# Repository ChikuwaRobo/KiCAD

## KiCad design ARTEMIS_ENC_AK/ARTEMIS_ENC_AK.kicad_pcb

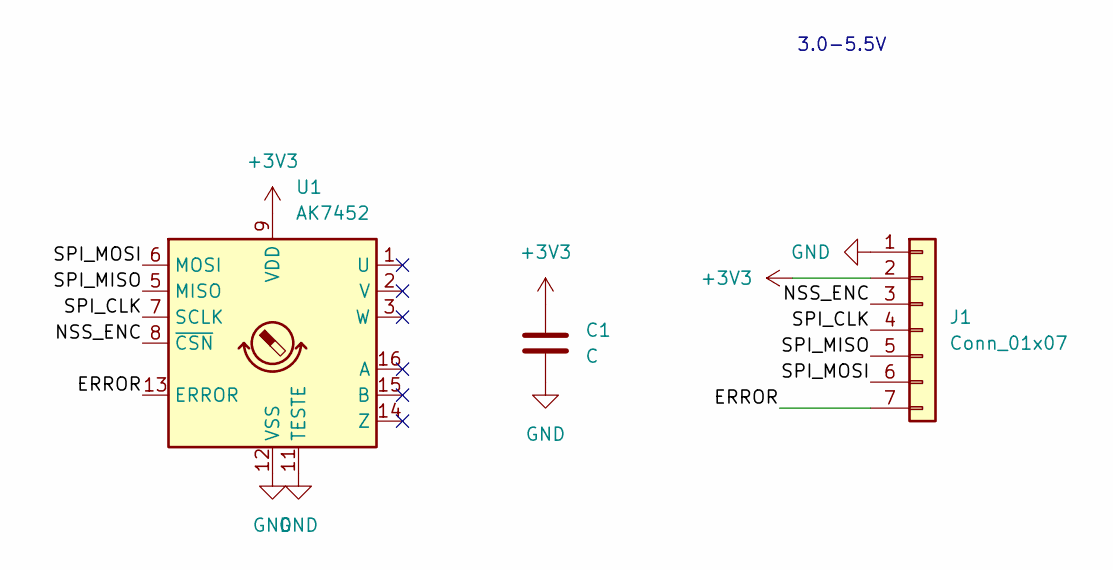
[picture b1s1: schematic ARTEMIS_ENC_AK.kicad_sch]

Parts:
C1: C; C_0603_1608Metric
J1: Conn_01x07; Hirose_DF13-07P-1.25DSA_1x07_P1.25mm_Vertical
U1: AK7452; TSSOP-16_4.4x5mm_P0.65mm

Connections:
+3V3: C1.1, J1.2, U1.9 (VDD)
/ERROR: J1.7, U1.13 (ERROR)
/NSS_ENC: J1.3, U1.8 (~CSN)
/SPI_CLK: J1.4, U1.7 (SCLK)
/SPI_MISO: J1.5, U1.5 (MISO)
/SPI_MOSI: J1.6, U1.6 (MOSI)
GND: C1.2, J1.1, U1.11 (TESTE), U1.12 (VSS)

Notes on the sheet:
3.0-5.5V

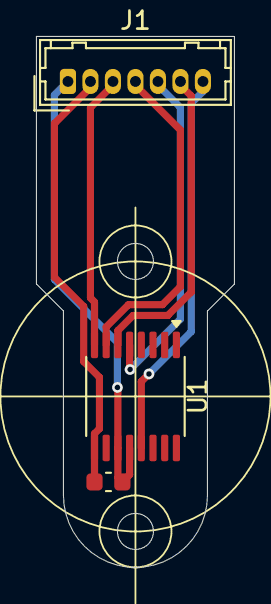
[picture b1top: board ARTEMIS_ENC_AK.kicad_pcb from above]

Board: 2 copper layers, 11.0 x 29.5 mm, 3 parts (0 on the bottom side), 7 nets.

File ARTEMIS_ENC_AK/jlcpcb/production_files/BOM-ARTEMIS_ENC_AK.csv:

Comment,Designator,Footprint,LCSC,Quantity
Conn_01x07,J1,Hirose_DF13-07P-1.25DSA_1x07_P1.25mm_Vertical,,1
AK7452,U1,TSSOP-16_4.4x5mm_P0.65mm,,1
C,C1,C_0603_1608Metric,,1

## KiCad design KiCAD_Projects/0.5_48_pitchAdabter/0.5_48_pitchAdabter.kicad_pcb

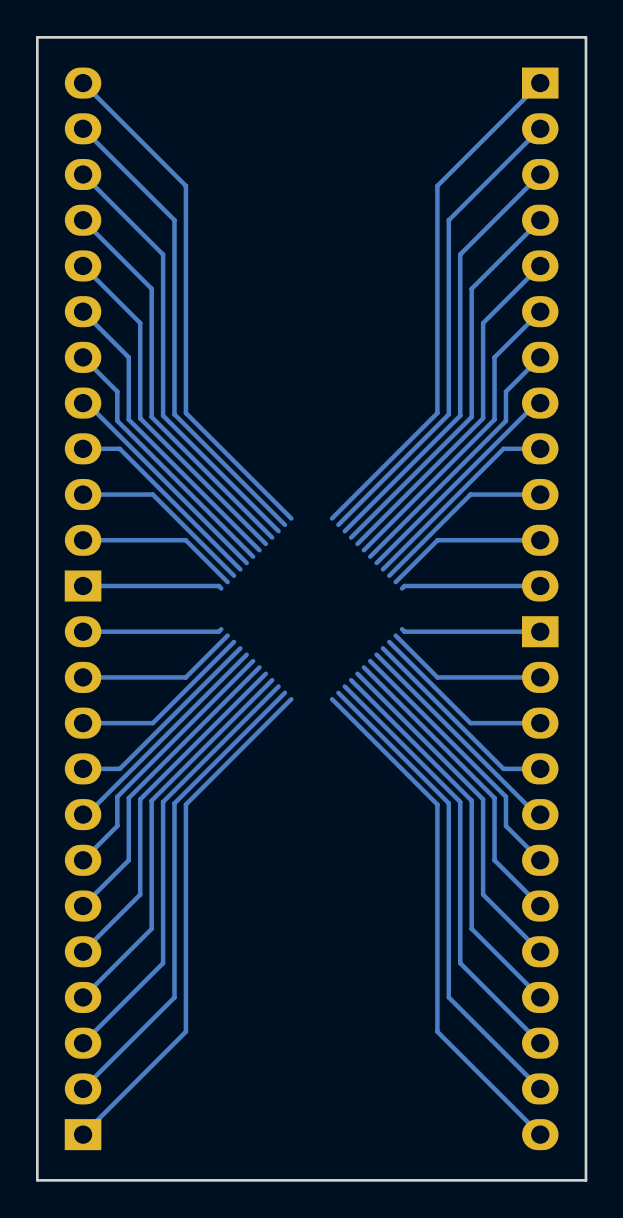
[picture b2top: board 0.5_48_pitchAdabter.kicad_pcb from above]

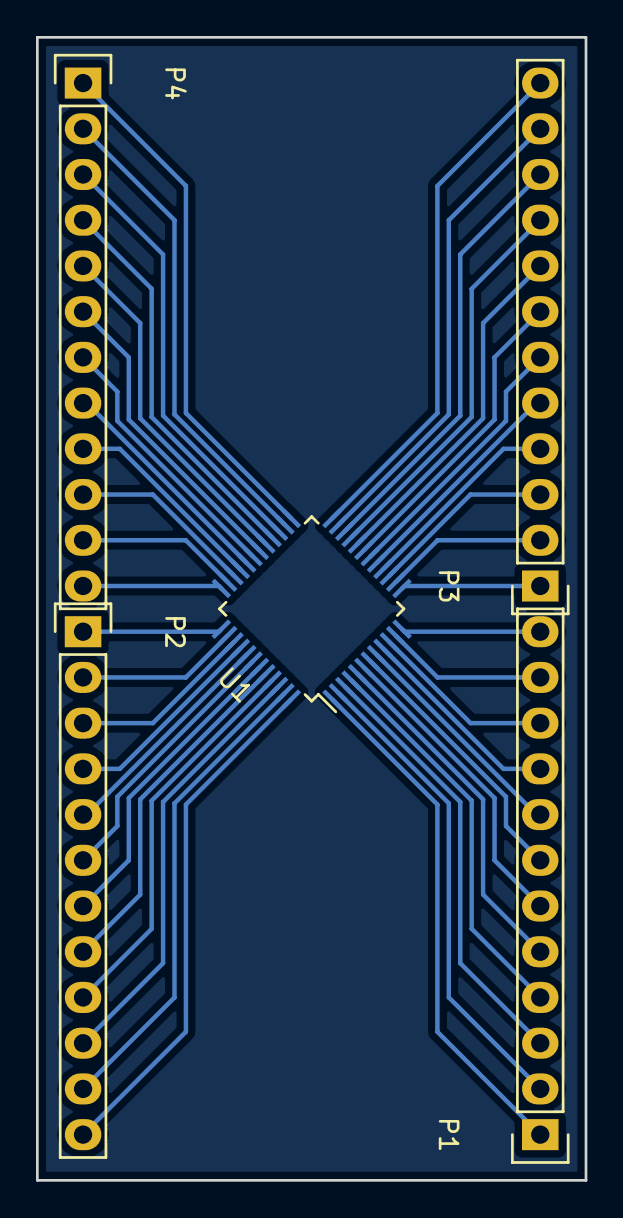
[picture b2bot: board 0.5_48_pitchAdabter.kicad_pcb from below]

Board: 2 copper layers, 30.5 x 63.5 mm, 5 parts (5 on the bottom side), 48 nets.

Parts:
P1, P2, P3, P4: CONN_01X12; Socket_Strip_Straight_1x12
U1: STM32F103_48; TQFP-48_7x7mm_Pitch0.5mm

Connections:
unnamed: P1.1, U1.1
unnamed: P1.2, U1.2
unnamed: P1.3, U1.3
unnamed: P1.4, U1.4
unnamed: P1.5, U1.5
unnamed: P1.6, U1.6
unnamed: P1.7, U1.7
unnamed: P1.8, U1.8
unnamed: P1.9, U1.9
unnamed: P1.10, U1.10
unnamed: P1.11, U1.11
unnamed: P1.12, U1.12
unnamed: P2.1, U1.37
unnamed: P2.2, U1.38
unnamed: P2.3, U1.39
unnamed: P2.4, U1.40
unnamed: P2.5, U1.41
unnamed: P2.6, U1.42
unnamed: P2.7, U1.43
unnamed: P2.8, U1.44
unnamed: P2.9, U1.45
unnamed: P2.10, U1.46
unnamed: P2.11, U1.47
unnamed: P2.12, U1.48
unnamed: P3.1, U1.13
unnamed: P3.2, U1.14
unnamed: P3.3, U1.15
unnamed: P3.4, U1.16
unnamed: P3.5, U1.17
unnamed: P3.6, U1.18
unnamed: P3.7, U1.19
unnamed: P3.8, U1.20
unnamed: P3.9, U1.21
unnamed: P3.10, U1.22
unnamed: P3.11, U1.23
unnamed: P3.12, U1.24
unnamed: P4.1, U1.25
unnamed: P4.2, U1.26
unnamed: P4.3, U1.27
unnamed: P4.4, U1.28
unnamed: P4.5, U1.29
unnamed: P4.6, U1.30
unnamed: P4.7, U1.31
unnamed: P4.8, U1.32
unnamed: P4.9, U1.33
unnamed: P4.10, U1.34
unnamed: P4.11, U1.35
unnamed: P4.12, U1.36

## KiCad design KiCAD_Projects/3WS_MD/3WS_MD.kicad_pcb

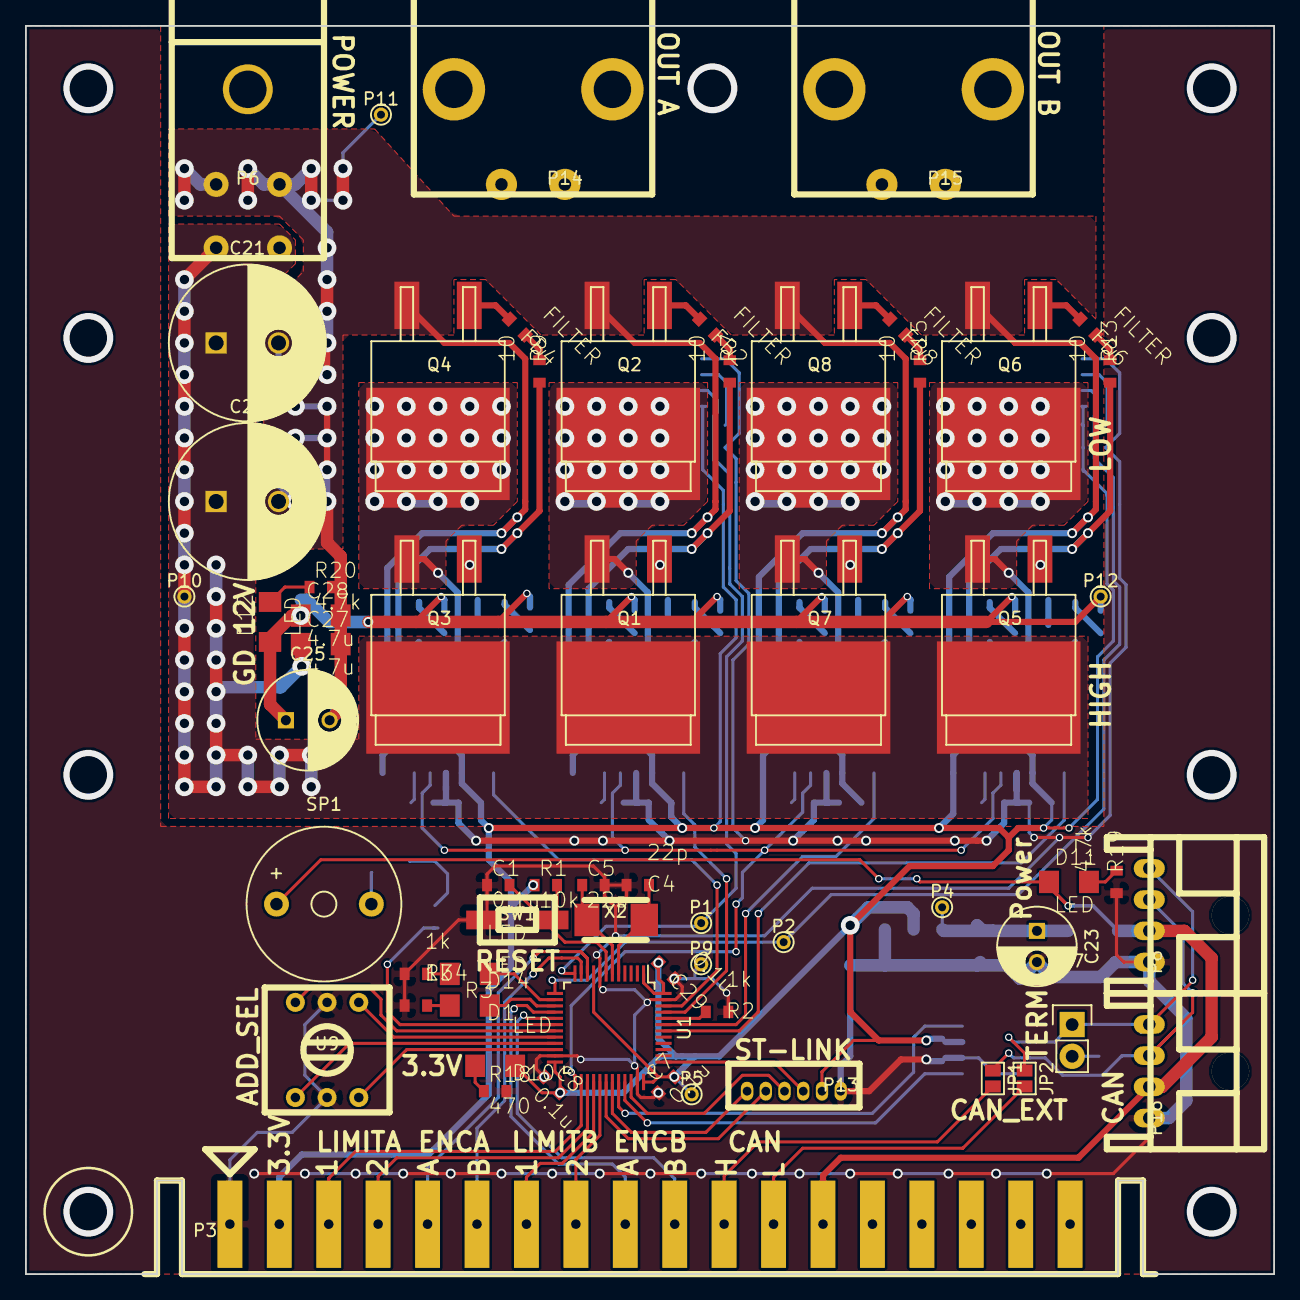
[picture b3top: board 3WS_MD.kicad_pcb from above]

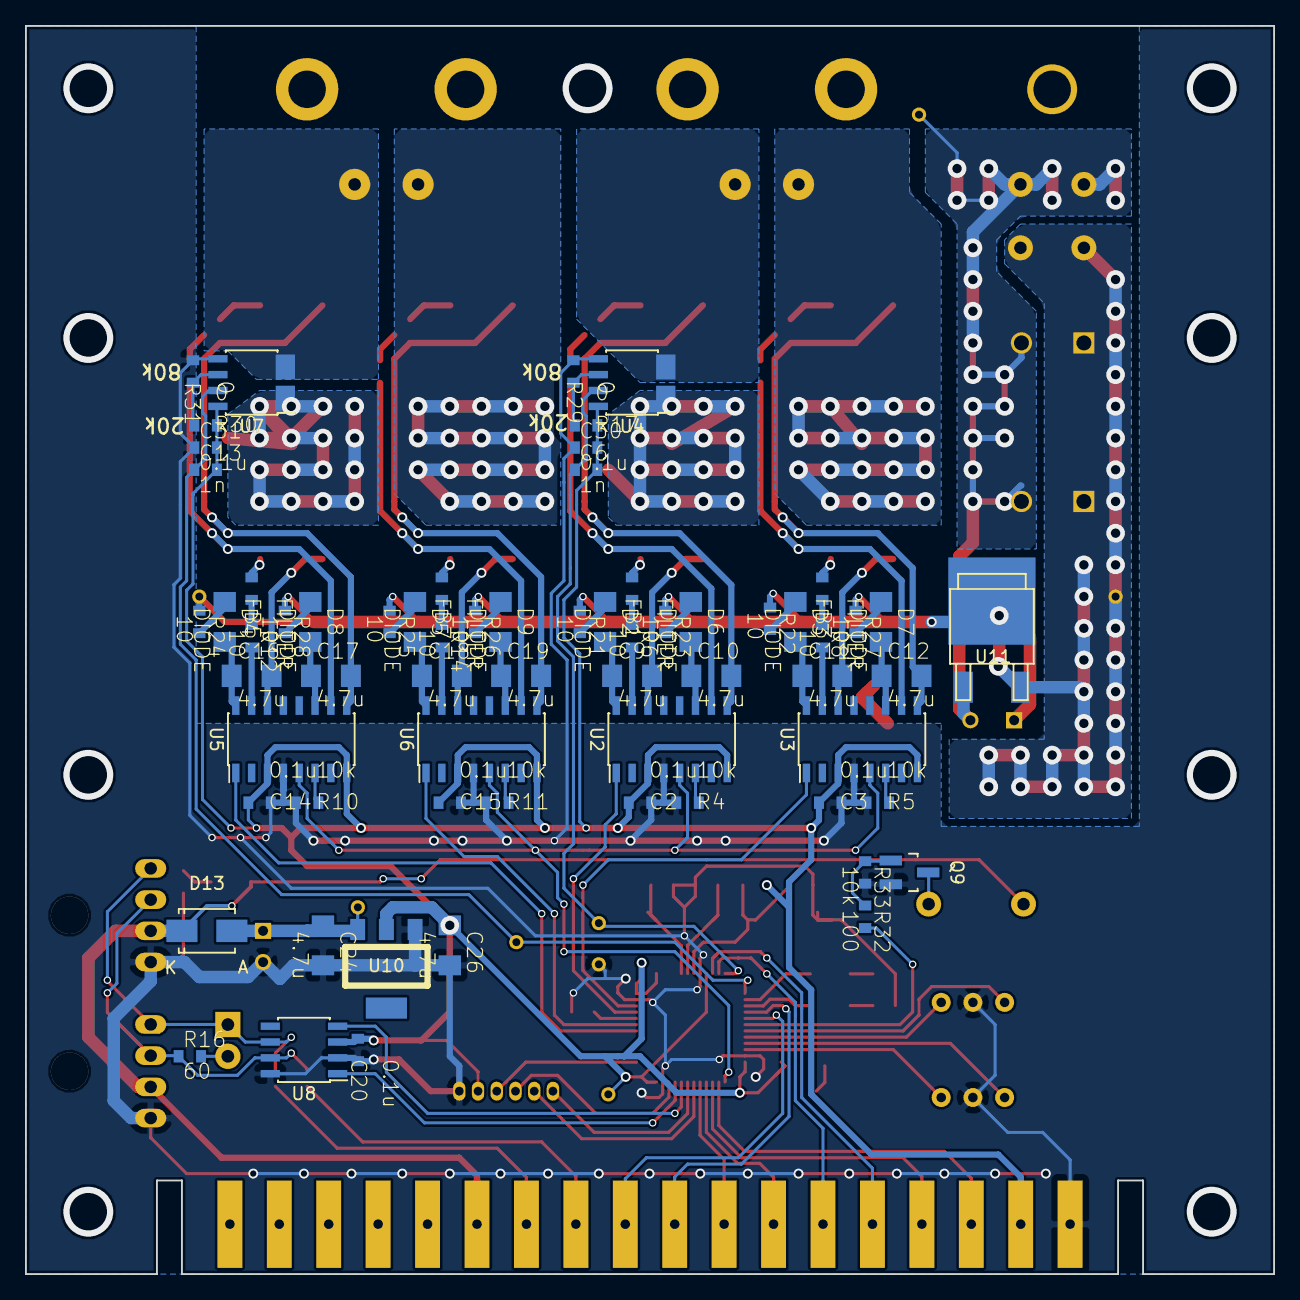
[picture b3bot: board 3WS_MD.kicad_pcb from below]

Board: 2 copper layers, 100.0 x 100.0 mm, 128 parts (65 on the bottom side), 103 nets.

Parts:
C1, C2, C3, C7, C8, C14, C15, C20, C29, C30, C31: 0.1u; C1608_WP
C4, C5: 22p; C1608_WP
C6, C13: 1n; C1608_WP
C9, C10, C11, C12, C16, C17, C18, C19, C24, C26, C27, C28: 4.7u; C3216
C21, C22: 470u; C_Radial_D12.5_L25_P5
C23: 100u; C_Radial_D6.3_L11.2_P2.5
C25: 100u; C_Radial_D8_L11.5_P3.5
D1, D10, D11, D12, D14: LED; C3216
D2, D3, D4, D5, D6, D7, D8, D9: DIODE; C3216
D13: DIODE; SMA_Standard
FB1, FB2, FB3, FB4, FB5, FB6, FB7, FB8: FILTER; C1608_WP
JP1, JP2: JUMPER; GS2
P1, P2, P4, P5, P9, P10, P11, P12: TST; PINTST
P3: CONN_01X18; CardEdge_22(44type)_3.96mm_M
P6: CONN_01X04; D-3500D_4S
P7: CONN_01X02; Pin_Header_Straight_1x02
P8, P16: CONN_01X04; XA_4LC
P13: CONN_01X06; ZH_6T
P14, P15: CONN_01X02; D-3200S_2L
Q1, Q2, Q3, Q4, Q5, Q6, Q7, Q8: MOSFET_N; D2-PAK
Q9: MOSFET_N; SOT-23_Handsoldering
R1, R4, R5, R10, R11, R33: 10k; C1608_WP
R2, R3, R34: 1k; C1608_WP
R6, R7, R8, R9, R12, R13, R14, R15, R21, R22, R23, R24, R25, R26, R27, R28: 10; C1608_WP
R16: 60; C1608_WP
R17, R29, R30, R31: 0; C1608_WP
R18: 470; C1608_WP
R19, R20: 4.7k; C1608_WP
R32: 100; C1608_WP
SP1: SPEAKER; Buzzer_12x9.5RM7.6
SW1: SW_PUSH; RP_SMD_Button
U1: STM32F103_48; LQFP-48_7x7mm_Pitch0.5mm
U2, U3, U5, U6: SI8234; SOIC-16_3.9x9.9mm_Pitch1.27mm
U4, U7: ACS722; SOIC-8_3.9x4.9mm_Pitch1.27mm_ACS
U8: MAX3051; SOIC-8_3.9x4.9mm_Pitch1.27mm
U9: SW_ROTARY_16; rotary_0F
U10: NCP1117ST33T3G; TO-223
U11: NCP1117ST12T3G; SOT-428
X2: CRYSTAL; ABM3_2pads

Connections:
+3.3V: C2.2, C3.2, C6.2, C7.2, C8.2, C13.2, C14.2, C15.2, C20.2, C26.1, C29.2, C30.2, C31.2, D10.1, P3.2, P5.1, P13.2, R1.1, R17.1, R30.1, U1.1, U1.9, U1.24, U1.36, U1.48, U2.3, U2.8, U3.3, U3.8, U4.8, U5.3, U5.8, U6.3, U6.8, U7.8, U8.3, U10.2
+12V: D11.1, D13.1, P3.13, P8.2, P16.2, SP1.1
+BATT: C21.1, C22.1, C27.1, P6.2, P6.4, P10.1, Q1.D, Q3.D, Q5.D, Q7.D, U11.3
/BOOT0: R2.2, U1.44
/BUZZER: R32.2, U1.18
/CANH: JP1.1, P8.3, P16.3, R16.1, U8.7
/CANL: JP2.1, P7.1, P8.4, P16.4, U8.6
/CAN_RX: U1.32, U8.4
/CAN_TX: U1.33, U8.1
/CURRENT_A: C6.1, P1.1, U1.12, U4.7
/CURRENT_B: C13.1, P2.1, U1.13, U7.7
/ENC_Aa: P3.5, U1.10
/ENC_Ab: P3.6, U1.11
/ENC_Ba: P3.9, U1.16
/ENC_Bb: P3.10, U1.17
/GD_12V: C25.1, C28.1, D12.1, P12.1, R21.1, R22.1, R23.1, R24.1, R25.1, R26.1, R27.1, R28.1, U11.2
/LED_A: D14.1, U1.14
/LED_B: D1.1, U1.15
/LIMIT_A1: P3.3, U1.26
/LIMIT_A2: P3.4, U1.27
/LIMIT_B1: P3.7, U1.28
/LIMIT_B2: P3.8, U1.29
/MOTOR_EN: U1.25, U2.5, U3.5, U5.5, U6.5
/NRST: C1.2, R1.2, SW1.2, U1.7
/OSC_IN: C4.1, U1.5, X2.1
/OSC_OUT: C5.1, U1.6, X2.2
/OUT_A: P14.1, U4.3, U4.4
/OUT_AN: C11.2, P14.2, Q3.S, Q4.D, U3.14
/OUT_B: P15.1, U7.3, U7.4
/OUT_BN: C18.2, P15.2, Q7.S, Q8.D, U6.14
/PWM_A: U1.45, U2.1
/PWM_AN: U1.46, U3.1
/PWM_B: U1.42, U5.1
/PWM_BN: U1.43, U6.1
/SEL_1: U1.19, U9.3
/SEL_2: U1.20, U9.1
/SEL_4: U1.21, U9.4
/SEL_8: U1.22, U9.6
/SWCLK: P13.3, U1.37
/SWDIO: P13.4, U1.34
/USART_RX: P13.6, U1.31
/USART_TX: P13.5, U1.30
GND: C1.1, C2.1, C3.1, C4.2, C5.2, C7.1, C8.1, C14.1, C15.1, C20.1, C23.2, C24.2, C26.2, C29.1, C30.1, C31.1, P3.1, P8.1, P9.1, P13.1, P16.1, Q9.S, R2.1, R3.2, R4.2, R5.2, R10.2, R11.2, R18.2, R19.2, R29.2, R31.2, R33.2, R34.2, SW1.1, U1.8, U1.23, U1.35, U1.47, U2.4, U3.4, U4.5, U5.4, U6.4, U7.5, U8.2, U8.8, U9.2, U9.5, U10.1
GNDPWR: C10.2, C12.2, C17.2, C19.2, C21.2, C22.2, C25.2, C27.2, C28.2, P6.1, P6.3, P11.1, Q2.S, Q4.S, Q6.S, Q8.S, R20.2, U2.9, U3.9, U5.9, U6.9, U11.1
unnamed: C9.1, D2.2, U2.16
unnamed: C9.2, Q1.S, Q2.D, U2.14, U4.1, U4.2
unnamed: C10.1, D6.2, U2.11
unnamed: C11.1, D3.2, U3.16
unnamed: C12.1, D7.2, U3.11
unnamed: C16.1, D4.2, U5.16
unnamed: C16.2, Q5.S, Q6.D, U5.14, U7.1, U7.2
unnamed: C17.1, D8.2, U5.11
unnamed: C18.1, D5.2, U6.16
unnamed: C19.1, D9.2, U6.11
unnamed: C23.1, C24.1, D13.2, P4.1, U10.3
unnamed: D1.2, R3.1
unnamed: D2.1, R21.2
unnamed: D3.1, R22.2
unnamed: D4.1, R24.2
unnamed: D5.1, R25.2
unnamed: D6.1, R23.2
unnamed: D7.1, R27.2
unnamed: D8.1, R28.2
unnamed: D9.1, R26.2
unnamed: D10.2, R18.1
unnamed: D11.2, R19.1
unnamed: D12.2, R20.1
unnamed: D14.2, R34.1
unnamed: FB1.1, R6.1
unnamed: FB1.2, Q1.G
unnamed: FB2.1, R7.1
unnamed: FB2.2, Q2.G
unnamed: FB3.1, R8.1
unnamed: FB3.2, Q3.G
unnamed: FB4.1, R9.1
unnamed: FB4.2, Q4.G
unnamed: FB5.1, R12.1
unnamed: FB5.2, Q5.G
unnamed: FB6.1, R13.1
unnamed: FB6.2, Q6.G
unnamed: FB7.1, R14.1
unnamed: FB7.2, Q7.G
unnamed: FB8.1, R15.1
unnamed: FB8.2, Q8.G
unnamed: JP1.2, P3.11
unnamed: JP2.2, P3.12
unnamed: P7.2, R16.2
unnamed: Q9.D, SP1.2
unnamed: Q9.G, R32.1, R33.1
unnamed: R4.1, U2.6
unnamed: R5.1, U3.6
unnamed: R6.2, U2.15
unnamed: R7.2, U2.10
unnamed: R8.2, U3.15
unnamed: R9.2, U3.10
unnamed: R10.1, U5.6
unnamed: R11.1, U6.6
unnamed: R12.2, U5.15
unnamed: R13.2, U5.10
unnamed: R14.2, U6.15
unnamed: R15.2, U6.10
unnamed: R17.2, R29.1, U4.6
unnamed: R30.2, R31.1, U7.6

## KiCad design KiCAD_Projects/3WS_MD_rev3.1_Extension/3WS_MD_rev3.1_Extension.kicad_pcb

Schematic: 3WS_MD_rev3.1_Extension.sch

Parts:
C1, C2, C3, C4, C5, C6, C11, C14, C15, C16, C17, C18: 0.1u; C1608_WP
C7, C8: 10n; C1608_WP
C9, C10: 22p; C1608_WP
C12, C13: 4.7u; C3216
D1, D2, D3, D4, D5, D6, D7, D8, D9: LED; LED_0603
ENC1, ENC2: RS422_ENCODER; DEF_ENCODER
IC1: TLP291; SOIJ-4_5.3x5.3mm_Pitch1.27mm
ISO1: ADuM3154; SSOP-20_5.3x7.2mm_Pitch0.65mm
JP1: JUMPER3; GS3
JP2, JP3: JUMPER; GS2
P1: CONN_01X04; Pin_Header_Straight_1x04
P2: CONN_02X06; Pin_Header_Straight_2x06
P3: CONN_02X04; Pin_Header_Straight_2x04
P4, P6: CONN_01X02; D-3200S_2L_PW
P5, P7: CONN_01X02; DEANS_T_M
P8: CONN_01X03; Pin_Header_Straight_1x03
P9: CONN_01X06; ZH_6T
Q1: MOSFET_N; SOT-23_Handsoldering
R1, R2, R3, R4: 120; C1608_WP
R5, R6, R7, R8, R11, R12, R20, R24, R25, R26, R27, R28: 4.7k; C1608_WP
R9, R15, R19: 10k; C1608_WP
R10: 18k; C2012
R13: 2.2k; C2012
R14: 10; C1608_WP
R16, R17: 1k; C1608_WP
R18, R22, R23: 100; C1608_WP
R21, R29, R30, R31, R32: 470; C1608_WP
SW1: SW_PUSH; RP_SMD_Button
U1: SN75175; SOIC-16_3.9x9.9mm_Pitch1.27mm
U2: LM358; SOIC-8_3.9x4.9mm_Pitch1.27mm
U3, U4: ACS758; ACS785xCB
U5: TBD62083A; SOIC-18_7.5x11.6mm_Pitch1.27mm
U6: STM32F103_48; LQFP-48_7x7mm_Pitch0.5mm
U7: NCP1117ST33T3G; SOT-223_reg
X1: CRYSTAL; ABM3_2pads

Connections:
+3.3V: C1.1, C3.1, C5.1, C17.1, D7.1 (A), ISO1.1, P1.2, U2.4 (V-), U3.1 (VCC), U4.1 (VCC)
+5V: C2.1, C4.1, C6.1, D5.1 (A), ENC1.2 (VCC), ENC2.2 (VCC), IC1.4, P2.3, U1.4 (1,2EN), U1.12 (3,4EN), U1.16 (VCC)
+12V: D1.1 (A), D2.1 (A), D3.1 (A), D4.1 (A), D6.1 (A), P2.2, P3.1, P3.3, P3.5, P3.7, U5.10 (COM)
+BATT: P8.3, R14.1
/BATT_IN: R10.2, R13.1, U6.18 (PB0/ADC12_IN8)
/ENC_Aa: P2.5, U1.3 (1Y)
/ENC_Aaa: ENC1.7 (~B), R1.2, U1.2 (1A)
/ENC_Aab: ENC1.8 (B), R1.1, U1.1 (1B)
/ENC_Ab: P2.7, U1.5 (2Y)
/ENC_Aba: ENC1.5 (~A), R2.1, U1.6 (2A)
/ENC_Abb: ENC1.6 (A), R2.2, U1.7 (2B)
/ENC_Ba: P2.9, U1.11 (3Y)
/ENC_Baa: ENC2.7 (~B), R4.2, U1.10 (3A)
/ENC_Bab: ENC2.8 (B), R4.1, U1.9 (3B)
/ENC_Bb: P2.11, U1.13 (4Y)
/ENC_Bba: ENC2.5 (~A), R3.1, U1.14 (4A)
/ENC_Bbb: ENC2.6 (A), R3.2, U1.15 (4B)
/EXIO_0: JP2.1, P1.3, U2.6 (-), U2.7
/EXIO_1: JP3.1, P1.4, U2.1, U2.2 (-)
/GD_12V: C12.1, D9.1 (A), P8.2, R17.1, U7.3 (VI)
/NRST: JP1.1, R15.2, SW1.1, U6.7 (NRST)
/OUT_0: P3.2, R5.2, U5.17 (OUT2), U5.18 (OUT1)
/OUT_1: P3.4, R6.2, U5.15 (OUT4), U5.16 (OUT3)
/OUT_2: P3.6, R7.2, U5.13 (OUT6), U5.14 (OUT5)
/OUT_3: P3.8, R8.2, U5.11 (OUT8), U5.12 (OUT7)
/PW_3.3V: C13.1, C14.1, C15.1, C16.1, C18.1, D8.1 (A), ISO1.20, JP1.3, R15.1, U6.1 (VBAT), U6.9 (VDDA), U6.24 (VDD_1), U6.36 (VDD_2), U6.48 (VDD_3), U7.2 (VO)
/SPI_MISO: ISO1.16, U6.16 (PA6/SPI1_MISO)
/SPI_MOSI: ISO1.17, U6.17 (PA7/SPI1_MOSI)
/SPI_NSS: ISO1.15, U6.14 (PA4/SPI1_NSS)
/SPI_SCK: ISO1.18, U6.15 (PA5/SPI1_SCK)
/SWDCK: P9.3, U6.37 (PA14/TCK/SWCLK)
/SWDIO: P9.4, U6.34 (PA13/TMS/SWDIO)
/USART_RX: P9.6, U6.32 (PA11/CAN_RX/USBDM)
/USART_TX: P9.5, U6.33 (PA12/CAN_TX/USBDP)
/V0A_IN: R27.1, R31.2, U6.12 (PA2/USART2_TX)
/V0B_IN: R28.1, R32.2, U6.13 (PA3/USART2_RX)
/V1A_IN: R26.1, R30.2, U6.10 (PA0/WKUP/ADC12_IN0)
/V1B_IN: R25.1, R29.2, U6.11 (PA1/ADC12_IN1)
/VALVE_0: ISO1.6, P2.12, U5.7 (IN7), U5.8 (IN8)
/VALVE_1: ISO1.3, P2.10, U5.5 (IN5), U5.6 (IN6)
/VALVE_2: ISO1.5, P2.8, U5.3 (IN3), U5.4 (IN4)
/VALVE_3: ISO1.4, P2.6, U5.1 (IN1), U5.2 (IN2)
/V_0A: P6.1, R27.2, U4.4 (IP+)
/V_0B: P6.2, P7.2, R28.2
/V_1A: P4.1, R26.2, U3.4 (IP+)
/V_1B: P4.2, P5.2, R25.2
/V_RX: IC1.3, P2.4, R16.1
/V_TX: R18.1, R19.2, U6.21 (PB10/USART3_TX/I2C_SCL)
GND: C1.2, C2.2, C3.2, C4.2, C5.2, C6.2, C7.2, C8.2, C17.2, ENC1.3 (GND), ENC2.3 (GND), ISO1.2, ISO1.7, ISO1.8, ISO1.10, P1.1, P2.1, R16.2, R20.2, R21.2, R22.2, U1.8 (GND), U2.8 (V+), U3.2 (GND), U4.2 (GND), U5.9 (GND)
GNDPWR: C9.1, C10.1, C11.2, C12.2, C13.2, C14.2, C15.2, C16.2, C18.2, ISO1.11, ISO1.19, P8.1, P9.1, Q1.S, R9.2, R13.2, R19.1, R23.2, R24.2, R29.1, R30.1, R31.1, R32.1, SW1.2, U6.8 (VSSA), U6.23 (VSS_1), U6.35 (VSS_2), U6.47 (VSS_3), U7.1 (GND)
unnamed: C7.1, JP3.2, R11.2, U2.3 (+)
unnamed: C8.1, JP2.2, R12.2, U2.5 (+)
unnamed: C9.2, U6.5 (PD0/OSC_IN), X1.1
unnamed: C10.2, U6.6 (PD1/OSC_OUT), X1.2
unnamed: C11.1, R10.1, R14.2
unnamed: D1.2 (K), R5.1
unnamed: D2.2 (K), R6.1
unnamed: D3.2 (K), R7.1
unnamed: D4.2 (K), R8.1
unnamed: D5.2 (K), R20.1
unnamed: D6.2 (K), R21.1
unnamed: D7.2 (K), R22.1
unnamed: D8.2 (K), R23.1
unnamed: D9.2 (K), R24.1
unnamed: IC1.1, R17.2
unnamed: IC1.2, Q1.D
unnamed: JP1.2, P9.2
unnamed: P5.1, U3.5 (IP-)
unnamed: P7.1, U4.5 (IP-)
unnamed: Q1.G, R18.2
unnamed: R9.1, U6.44 (BOOT0)
unnamed: R11.1, U3.3 (VIOUT)
unnamed: R12.1, U4.3 (VIOUT)

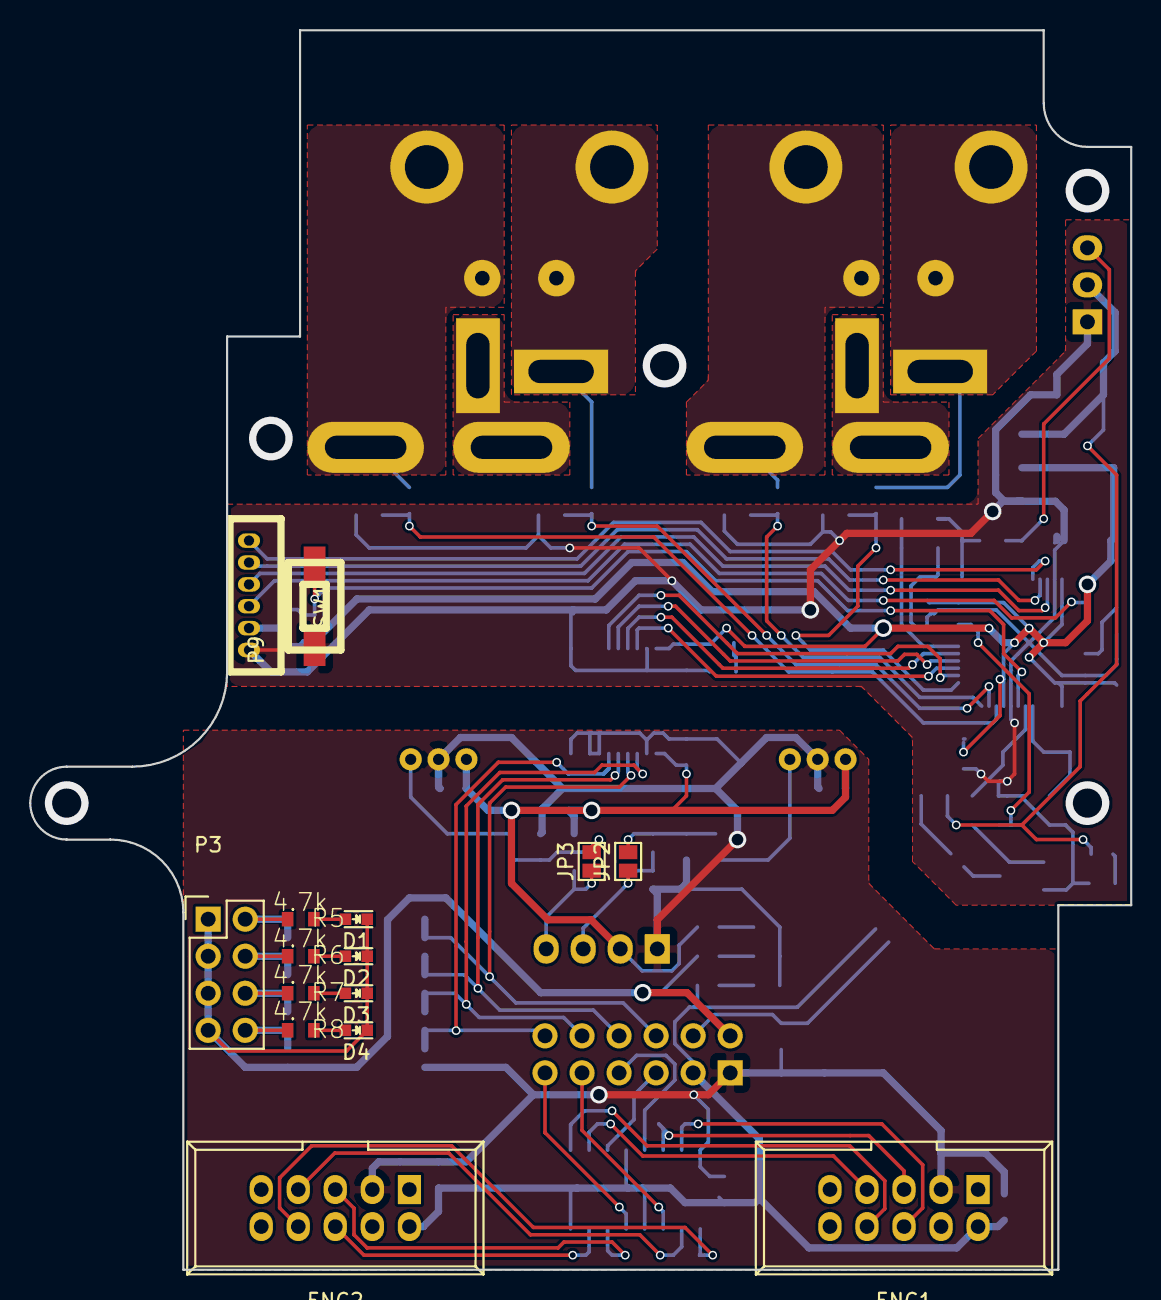
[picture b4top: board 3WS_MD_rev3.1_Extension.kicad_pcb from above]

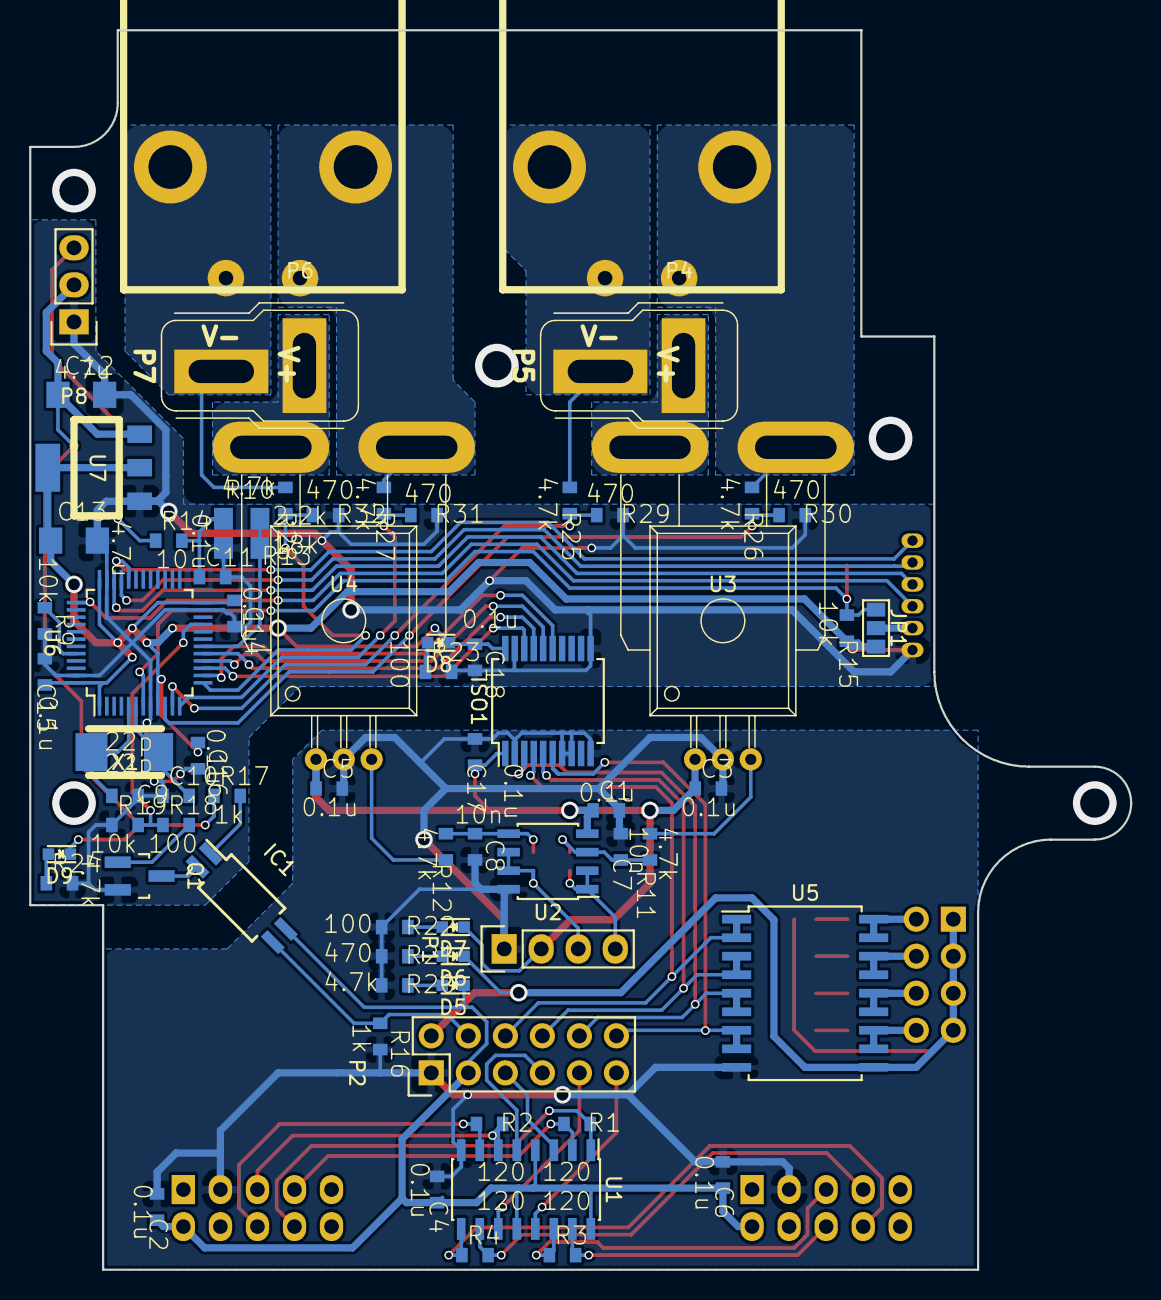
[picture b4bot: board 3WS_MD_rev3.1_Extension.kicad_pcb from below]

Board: 2 copper layers, 75.5 x 85.0 mm, 85 parts (70 on the bottom side), 73 nets.
